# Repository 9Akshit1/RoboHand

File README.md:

# RoboHand
DESCRIPTION: RoboHand is just like how it sounds. It is a robotic hand with five fingers that can mimic real hand movements. It uses small servo motors controlled by a smart camera board to copy gestures like fists or peace signs. The hand can also be controlled manually via a computer or preset motions for easy testing and flexibility.

INSPIRATION: I've always been inspired by how human hands move and wanted to recreate that motion using motors and tendons. Additionally, at the same time, I was learning how to simulate robots in physics based simulations called MuJoCo, which is why I wanted to also actaully build a hand and test my inverse kinematics coding knowledge at it.

Note: I am currently working on polishing the CAD, so it's much thinner, models the human hand better, and allows for full movement!

# Final CAD
The separate finger files and body files are in ther CAD folder. The full built hand CAD File is called RoboHand.stl in the CAD folder. 

The below five images are each finger's separated pieces. They are all essentially copies of the Middle_Finger.stl file, except they have been scaled to be shorter. 

Also, please note that I can always just add supports before I 3D print, so we do not need to worry about that!

Middle Finger (the original finger):

Thumb Finger (a scaled down version of the middle finger):

Index Finger (a scaled down version of the middle finger):

Ring Finger (a scaled down version of the middle finger):

Pinky Finger (a scaled down version of the middle finger):

Also, note that for the below hand-body/palm separated image, none of the parts are touching but they are very close to each other. That is just temporary. When I actually 3D print everything, I will separate those parts into different CAD files.

This is what the full build hand will look like. I will likely hot glue every piece together. 

# Final Circuit Schematic
Schematic is called robohand.kicad_sch in the schematic_pcb/robohand folder. While this shows 4 EMG sensors (the ESP32-CAM doesnt have enough pins), I actually need 9 EMG sensors to fluidly control a human hand and train it to be extremely good at autonomous imitation. Since the ESP32-CAM doesn't have enough pins, I decided to use the board setup I will be getting from my RoboArm project. That project has enough pins for me to connect all of my EMG sensors. 

# Final Firmware Stuff
The firmware software is in the firmware folder, and are called esp32_ver.py (which will be used on the ESP32-CAM board), and pc_ver.py (which can be tested on a PC).

## Bill of Materials (BOM)

| Item                             | Quantity | Total Cost (USD) | Description / Part Number                      | Notes                                | Links                             |
|---------------------------------|----------|-------------------|-----------------------------------------------|-------------------------------------|-------------------------|
| **ESP32-CAM module**             | 1        | $9.04 | ESP32-CAM Module                | Main controller + camera             | https://www.aliexpress.com/item/1005006341099716.html?spm=a2g0o.productlist.main.4.10b31f44f3CRYE&algo_pvid=cf5cc23f-74d1-44a8-bcb2-311bc13f1dcc&algo_exp_id=cf5cc23f-74d1-44a8-bcb2-311bc13f1dcc-3&pdp_ext_f=%7B%22order%22%3A%22103%22%2C%22eval%22%3A%221%22%7D&pdp_npi=4%40dis%21CAD%212.83%211.63%21%21%2114.42%218.32%21%402101d9ee17540044723562302eab01%2112000036821212387%21sea%21CA%216438900822%21ABX&curPageLogUid=s9SbCAg5Mvaq&utparam-url=scene%3Asearch%7Cquery_from%3A |
| **ESP32-CAM DEV Board**             | 1        | $2.08 | ESP32-CAM DEV Board                | Needed to actualyl conenct ESP32 and program it            | https://www.aliexpress.com/item/1005006341099716.html?spm=a2g0o.productlist.main.4.10b31f44f3CRYE&algo_pvid=cf5cc23f-74d1-44a8-bcb2-311bc13f1dcc&algo_exp_id=cf5cc23f-74d1-44a8-bcb2-311bc13f1dcc-3&pdp_ext_f=%7B%22order%22%3A%22103%22%2C%22eval%22%3A%221%22%7D&pdp_npi=4%40dis%21CAD%212.83%211.63%21%21%2114.42%218.32%21%402101d9ee17540044723562302eab01%2112000036821212387%21sea%21CA%216438900822%21ABX&curPageLogUid=s9SbCAg5Mvaq&utparam-url=scene%3Asearch%7Cquery_from%3A |
| **MG90S Servo Motor**            | 10        | $20.99 | Metal Gear Micro Servo, 9g                     | Cheapest price servo motor. Need 3 for thumb, because it has that many DOF and each of those are important. We have 4 motors for the lower section's movement of the other fingers. Ideally, I wouldve wanted another 4 more motors so I could control the middle section's movement of the other fingers, but the aliexpress link only allows me to buy 3 more, so I'll need to buy another one on my own later. In the CAD, 5 can be seen directly, but there will actually be 6 more contained within the hand and the arm to controll all of my DOF.                     | https://www.aliexpress.com/item/1005008626768357.html?spm=a2g0o.productlist.main.2.7f2015caxNFEhm&aem_p4p_detail=202507311630421114710384897480003208335&algo_pvid=f808fc16-865d-4975-95a1-d6fab4f69bc5&algo_exp_id=f808fc16-865d-4975-95a1-d6fab4f69bc5-1&pdp_ext_f=%7B%22order%22%3A%22317%22%2C%22eval%22%3A%221%22%7D&pdp_npi=4%40dis%21CAD%215.83%211.63%21%21%214.12%211.15%21%402101c59517540046428904607ef048%2112000046009069094%21sea%21CA%216438900822%21ABX&curPageLogUid=JxTQbST0aPKs&utparam-url=scene%3Asearch%7Cquery_from%3A&search_p4p_id=202507311630421114710384897480003208335_1 |
| **Electrolytic Capacitor 1000µF, 10V** | 1        | $3.21 | Radial leaded capacitor                        | Power filtering. The link has 10 pcs but there was no other product that only sold 1 piece and this was the cheapest  | https://www.aliexpress.com/item/33010665515.html?spm=a2g0o.productlist.main.19.5696e336YqdJ1M&algo_pvid=05eaeade-4550-4688-b75d-17b6cb5b207e&algo_exp_id=05eaeade-4550-4688-b75d-17b6cb5b207e-18&pdp_ext_f=%7B%22order%22%3A%2270%22%2C%22eval%22%3A%221%22%7D&pdp_npi=4%40dis%21CAD%214.37%211.63%21%21%213.09%211.15%21%402101ef5e17540057514022423e8084%2167121829359%21sea%21CA%216438900822%21ABX&curPageLogUid=NYzuwQWBHlT4&utparam-url=scene%3Asearch%7Cquery_from%3A |
| **Male/Female Jumper Wires**     | ~15      | N/A| Dupont cables (already owned)                                 | For wiring servos, buttons, ESP32   | N/A |
| **Female Power Adapter DC Barrel to Screw Plug Jack Connector** | 1 | $2.52 | Mr.Geeker 10 Pcs Female Power Adapter DC Barrel to Screw Plug Jack Connector 2.1x5.5mm | Used to connect the power adapter to the ESP32-CAM board but manage the power and GND. The product link was the cheapest deal I could find | https://www.aliexpress.com/item/1005008987005268.html?spm=a2g0o.productlist.main.2.df155998nLKCjG&aem_p4p_detail=202508011402373093864537015840004227846&algo_pvid=96a38800-3a1a-4c03-b19f-4abbd7d5611a&algo_exp_id=96a38800-3a1a-4c03-b19f-4abbd7d5611a-1&pdp_ext_f=%7B%22order%22%3A%2229%22%2C%22eval%22%3A%221%22%7D&pdp_npi=4%40dis%21CAD%213.43%211.63%21%21%2117.48%218.31%21%402101e9ec17540821576896587efa3e%2112000047469895587%21sea%21CA%216438900822%21ABX&curPageLogUid=bBj4EJuoberQ&utparam-url=scene%3Asearch%7Cquery_from%3A&search_p4p_id=202508011402373093864537015840004227846_1 |
| **EMG Sensors** | Muscle BioAmp Candy | 9 | $89.91 | Muscle activity sensors. These are one of the best quality sensors suitable for research projects such as this and are also the cheapest deal I found everywhere! I need 9 because I'm doing a full hand, where each finger has around 2 DOF, except the thumb which has 3 and the pinky which I decided to let it have only 1 EMG since its muscles are highly connected with the other fingers. | https://www.tindie.com/products/upsidedownlabs/muscle-bioamp-candy-emg-sensor/ |
| **ADC Modules** | ADS1115 | 1 | $1.97 | 16-bit ADC | https://www.aliexpress.com/item/1005007628692389.html?spm=a2g0o.productlist.main.2.6c913e84NYJmIs&aem_p4p_detail=202507311619095829272559576480003213401&algo_pvid=1275a360-73ba-4ddf-a858-0478d2ddf380&algo_exp_id=1275a360-73ba-4ddf-a858-0478d2ddf380-1&pdp_ext_f=%7B%22order%22%3A%22612%22%2C%22eval%22%3A%221%22%7D&pdp_npi=4%40dis%21CAD%2111.18%216.23%21%21%2156.85%2131.67%21%40210313e917540039492598181eaff1%2112000041563143884%21sea%21CA%216438900822%21ABX&curPageLogUid=H8gnUD0dSVdM&utparam-url=scene%3Asearch%7Cquery_from%3A&search_p4p_id=202507311619095829272559576480003213401_1 |

**BOM Cost:** $129.72 USD ≈ $176.73 CAD            

**Shipping:** $14.91 USD ≈ $20.31 CAD     --- The cost comes from the EMG sensors. Everything else is FREE SHIPPING becuase this will be my frist ever order on Aliexpress

**Taxes (in  Ontario, Canada, it's 13%):** $18.80 USD ≈ $25.62 CAD

**Total Cost:** $163.43 USD ≈ $222.66 CAD

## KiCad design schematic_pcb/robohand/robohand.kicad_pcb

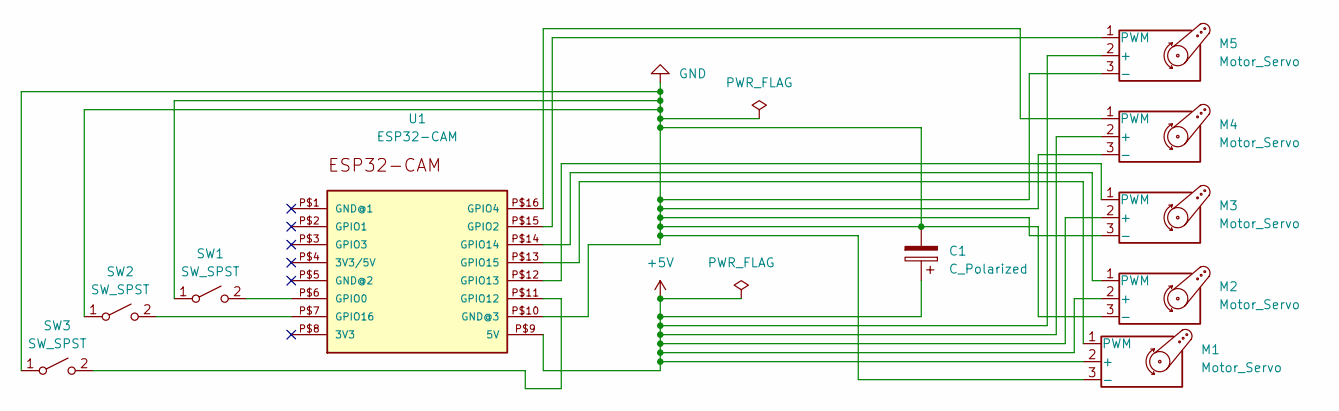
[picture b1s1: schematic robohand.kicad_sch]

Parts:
C1: C_Polarized; CP_Radial_D5.0mm_P2.50mm
M1, M2, M3, M4, M5: Motor_Servo; PinHeader_1x03_P2.54mm_Vertical
SW1, SW2, SW3: SW_SPST; SW_PUSH_6mm_H5mm
U1: ESP32-CAM

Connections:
+5V: C1.1, M1.2 (+), M2.2 (+), M3.2 (+), M4.2 (+), M5.2 (+), U1.P$9 (5V)
GND: C1.2, M1.3 (-), M2.3 (-), M3.3 (-), M4.3 (-), M5.3 (-), SW1.1 (A), SW2.1 (A), SW3.1 (A), U1.P$10 (GND@3)
unnamed: M1.1 (PWM), U1.P$13 (GPIO15)
unnamed: M2.1 (PWM), U1.P$14 (GPIO14)
unnamed: M3.1 (PWM), U1.P$12 (GPIO13)
unnamed: M4.1 (PWM), U1.P$16 (GPIO4)
unnamed: M5.1 (PWM), U1.P$15 (GPIO2)
unnamed: SW1.2 (B), U1.P$6 (GPIO0)
unnamed: SW2.2 (B), U1.P$7 (GPIO16)
unnamed: SW3.2 (B), U1.P$11 (GPIO12)

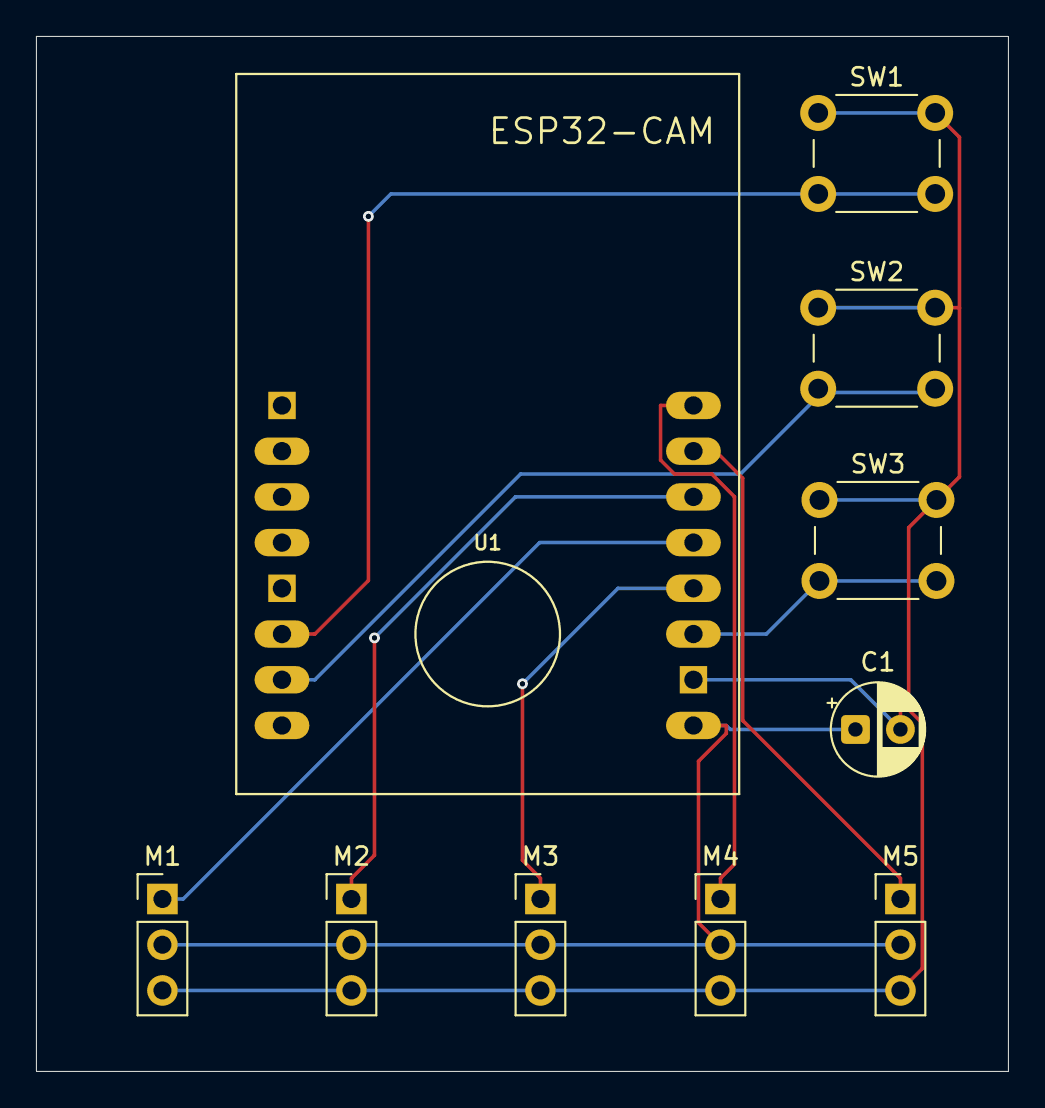
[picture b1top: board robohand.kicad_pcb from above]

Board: 2 copper layers, 54.0 x 57.5 mm, 10 parts (0 on the bottom side), 10 nets.

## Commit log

2025-06-28 uplaoded the CAD file
2025-06-30 schematic done
2025-06-30 edited journal
2025-07-02 full CAD hand done
2025-07-02 july 2nd
2025-07-04 july 3rd mainly coding firmware hand tracking
2025-07-04 july 3rd mainly coding hand tracking firmware
2025-07-05 july 4th mainly CAD fixing
2025-07-17 deleted .3mf file
2025-07-26 edited readme and fixed esp32 library issue
2025-08-07 august 6th - some schematci and BOM editing
